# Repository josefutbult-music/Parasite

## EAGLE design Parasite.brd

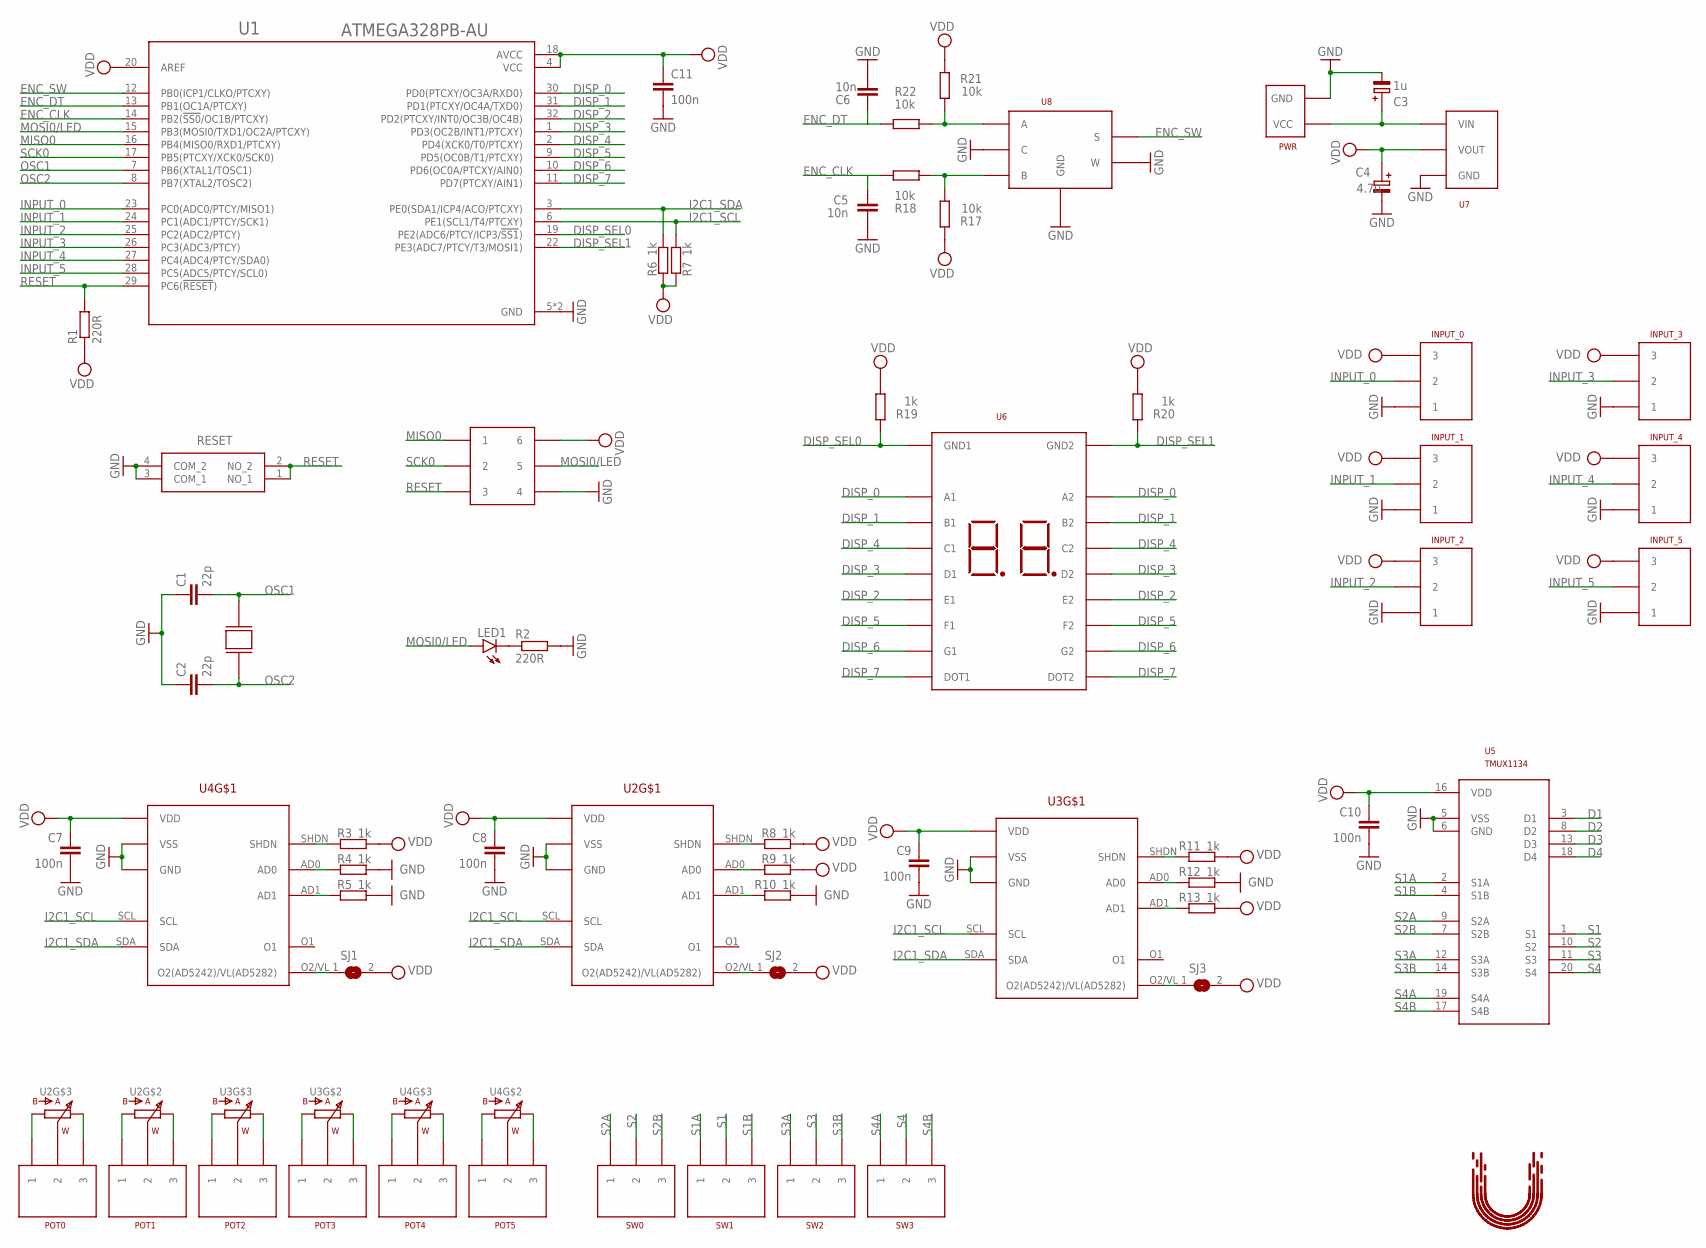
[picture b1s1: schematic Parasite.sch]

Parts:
C1, C2: 22p; C-1206
C3: 1u; UD-4X5,8_NICHICON
C4: 4.7u; UD-4X5,8_NICHICON
C5, C6: 10n; C-1206
C7, C8, C9, C10, C11: 100n; C-1206
INPUT_0, INPUT_1, INPUT_2, INPUT_3, INPUT_4, INPUT_5: 3_PIN_CONNECTOR
LED1: LEDLED_THROUGH; LED3MM
POT0, POT1, POT2, POT3, POT4, POT5: 3_PIN_CONNECTOR
PWR: PWR
R1, R2: 220R; R1206
R3, R4, R5, R6, R7, R8, R9, R10, R11, R12, R13, R19, R20: 1k; R1206
R17, R18, R21, R22: 10k; R1206
RESET: BUTTON; PTS647SK38SMTR2LFS
SJ1, SJ2, SJ3: JUMPER; SJ
SW0, SW1, SW2, SW3: 3_PIN_CONNECTOR
U1: ATMEGA328PB-AU; QFP80P900X900X120-32N
U2, U4: DIGITAL_POT_AD5242AD5242/AD5282; SOP65P640X120-16N
U3: DIGITAL_POT_AD5282AD5242/AD5282; SOP65P640X120-16N
U5: TMUX1134; SOP65P640X120-20N
U6: 7_SEGMENT_DISPLAY
U7: VOLTAGE_REGULATOR_LDL1117S50RVOLTAGE_REGULATOR_LD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; SOT230P700X180-4N
U8: ROTARY_ENCODER; ENCODER_PEC11H-4220F
U9: 3X2_PINHEADER3X2_PINHEADER; HDRV6W64P254_2X3_900X508X838B
U10: CRYSTAL_LFXTAL027946BULKCRYSTAL_LFXTAL027946BULK; XTAL1140X490X430N
U$5: UTBULT_DESIGN2; UD_2

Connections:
D1: U5.3 (D1)
D2: U5.8 (D2)
D3: U5.13 (D3)
D4: U5.18 (D4)
DISP_0: U1.30 (PD0(PTCXY/OC3A/RXD0)), U6.A1, U6.A2
DISP_1: U1.31 (PD1(PTCXY/OC4A/TXD0)), U6.B1, U6.B2
DISP_2: U1.32 (PD2(PTCXY/INT0/OC3B/OC4B)), U6.E1, U6.E2
DISP_3: U1.1 (PD3(OC2B/INT1/PTCXY)), U6.D1, U6.D2
DISP_4: U1.2 (PD4(XCK0/T0/PTCXY)), U6.C1, U6.C2
DISP_5: U1.9 (PD5(OC0B/T1/PTCXY)), U6.F1, U6.F2
DISP_6: U1.10 (PD6(OC0A/PTCXY/AIN0)), U6.G1, U6.G2
DISP_7: U1.11 (PD7(PTCXY/AIN1)), U6.DOT1, U6.DOT2
DISP_SEL0: R19.1, U1.19 (PE2(ADC6/PTCY/ICP3/!SS1!)), U6.GND1
DISP_SEL1: R20.1, U1.22 (PE3(ADC7/PTCY/T3/MOSI1)), U6.GND2
ENC_CLK: C5.P$2 (2), R18.2, U1.14 (PB2(!SS0!/OC1B/PTCXY))
ENC_DT: C6.P$2 (2), R22.2, U1.13 (PB1(OC1A/PTCXY))
ENC_SW: U1.12 (PB0(ICP1/CLKO/PTCXY)), U8.S
GND: C1.P$1 (1), C2.P$1 (1), C3.-, C4.-, C5.P$1 (1), C6.P$1 (1), C7.P$2 (2), C8.P$2 (2), C9.P$2 (2), C10.P$2 (2), C11.P$2 (2), INPUT_0.P$1 (1), INPUT_1.P$1 (1), INPUT_2.P$1 (1), INPUT_3.P$1 (1), INPUT_4.P$1 (1), INPUT_5.P$1 (1), PWR.P$2 (GND), R2.2, R4.1, R5.1, R10.1, R12.1, RESET.3 (COM_1), RESET.4 (COM_2), U1.5 (GND), U1.21 (GND), U2.GND, U2.VSS, U3.GND, U3.VSS, U4.GND, U4.VSS, U5.5 (VSS), U5.6 (GND), U7.1 (GND), U8.C, U8.GND1 (GND), U8.GND2 (GND), U8.W, U9.4
I2C1_SCL: R7.1, U1.6 (PE1(SCL1/T4/PTCXY)), U2.SCL, U3.SCL, U4.SCL
I2C1_SDA: R6.1, U1.3 (PE0(SDA1/ICP4/ACO/PTCXY)), U2.SDA, U3.SDA, U4.SDA
INPUT_0: INPUT_0.P$2 (2), U1.23 (PC0(ADC0/PTCY/MISO1))
INPUT_1: INPUT_1.P$2 (2), U1.24 (PC1(ADC1/PTCY/SCK1))
INPUT_2: INPUT_2.P$2 (2), U1.25 (PC2(ADC2/PTCY))
INPUT_3: INPUT_3.P$2 (2), U1.26 (PC3(ADC3/PTCY))
INPUT_4: INPUT_4.P$2 (2), U1.27 (PC4(ADC4/PTCY/SDA0))
INPUT_5: INPUT_5.P$2 (2), U1.28 (PC5(ADC5/PTCY/SCL0))
MISO0: U1.16 (PB4(MISO0/RXD1/PTCXY)), U9.1
MOSI0/LED: LED1.A, U1.15 (PB3(MOSI0/TXD1/OC2A/PTCXY)), U9.5
unnamed: LED1.K (C), R2.1
unnamed: R3.2, U4.SHDN
unnamed: R4.2, U4.AD0
unnamed: R5.2, U4.AD1
unnamed: SJ1.1, U4.O2/VL (O2(AD5242)/VL(AD5282))
unnamed: R11.2, U3.SHDN
unnamed: R8.2, U2.SHDN
unnamed: R9.2, U2.AD0
unnamed: R10.2, U2.AD1
unnamed: SJ2.1, U2.O2/VL (O2(AD5242)/VL(AD5282))
unnamed: R12.2, U3.AD0
unnamed: R13.2, U3.AD1
unnamed: SJ3.1, U3.O2/VL (O2(AD5242)/VL(AD5282))
unnamed: POT2.P$2 (2), U3.W2 (W)
unnamed: POT1.P$2 (2), U2.W1 (W)
unnamed: POT0.P$2 (2), U2.W2 (W)
unnamed: POT4.P$2 (2), U4.W2 (W)
unnamed: POT5.P$2 (2), U4.W1 (W)
unnamed: POT3.P$2 (2), U3.W1 (W)
unnamed: POT0.P$3 (3), U2.A2 (A)
unnamed: POT0.P$1 (1), U2.B2 (B)
unnamed: POT3.P$1 (1), U3.B1 (B)
unnamed: POT3.P$3 (3), U3.A1 (A)
unnamed: POT2.P$1 (1), U3.B2 (B)
unnamed: POT2.P$3 (3), U3.A2 (A)
unnamed: POT1.P$1 (1), U2.B1 (B)
unnamed: POT1.P$3 (3), U2.A1 (A)
unnamed: POT4.P$3 (3), U4.A2 (A)
unnamed: POT5.P$3 (3), U4.A1 (A)
unnamed: POT4.P$1 (1), U4.B2 (B)
unnamed: POT5.P$1 (1), U4.B1 (B)
unnamed: C3.+, PWR.P$1 (VCC), U7.3 (VIN)
unnamed: R17.2, R18.1, U8.B
unnamed: R21.2, R22.1, U8.A
OSC1: C1.P$2 (2), U1.7 (PB6(XTAL1/TOSC1)), U10.2
OSC2: C2.P$2 (2), U1.8 (PB7(XTAL2/TOSC2)), U10.1
RESET: R1.2, RESET.1 (NO_1), RESET.2 (NO_2), U1.29 (PC6(!RESET!)), U9.3
S1: SW1.P$2 (2), U5.1 (S1)
S1A: SW1.P$1 (1), U5.2 (S1A)
S1B: SW1.P$3 (3), U5.4 (S1B)
S2: SW0.P$2 (2), U5.10 (S2)
S2A: SW0.P$1 (1), U5.9 (S2A)
S2B: SW0.P$3 (3), U5.7 (S2B)
S3: SW2.P$2 (2), U5.11 (S3)
S3A: SW2.P$1 (1), U5.12 (S3A)
S3B: SW2.P$3 (3), U5.14 (S3B)
S4: SW3.P$2 (2), U5.20 (S4)
S4A: SW3.P$1 (1), U5.19 (S4A)
S4B: SW3.P$3 (3), U5.17 (S4B)
SCK0: U1.17 (PB5(PTCXY/XCK0/SCK0)), U9.2
VDD: C4.+, C7.P$1 (1), C8.P$1 (1), C9.P$1 (1), C10.P$1 (1), C11.P$1 (1), INPUT_0.P$3 (3), INPUT_1.P$3 (3), INPUT_2.P$3 (3), INPUT_3.P$3 (3), INPUT_4.P$3 (3), INPUT_5.P$3 (3), R1.1, R3.1, R6.2, R7.2, R8.1, R9.1, R11.1, R13.1, R17.1, R19.2, R20.2, R21.1, SJ1.2, SJ2.2, SJ3.2, U1.4 (VCC), U1.18 (AVCC), U1.20 (AREF), U2.VDD, U3.VDD, U4.VDD, U5.16 (VDD), U7.2 (VOUT), U7.4 (VOUT), U9.6

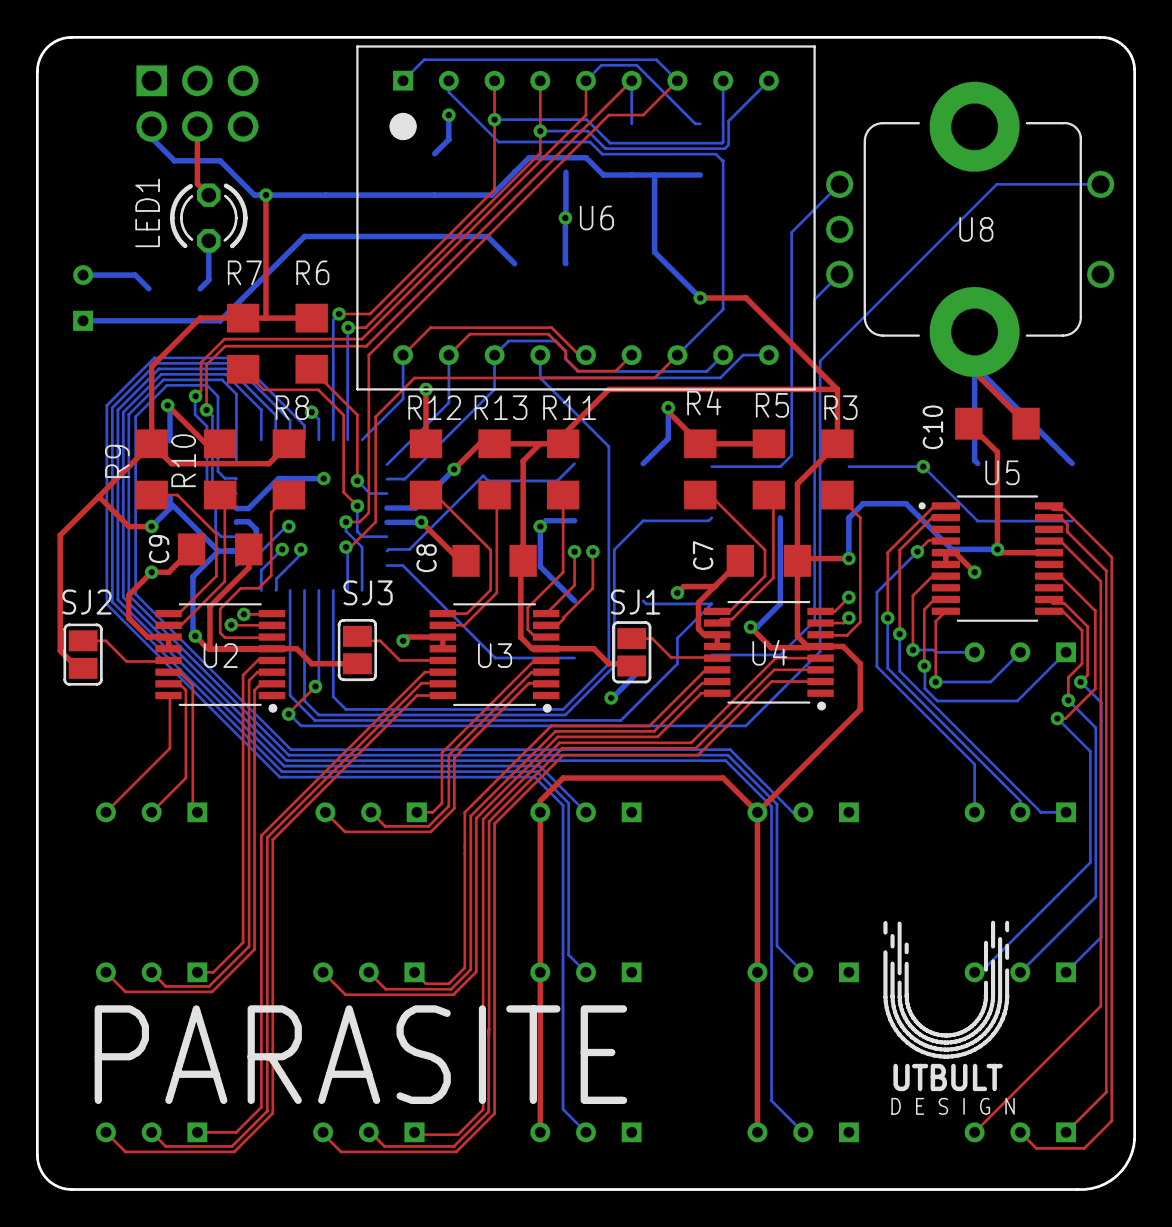
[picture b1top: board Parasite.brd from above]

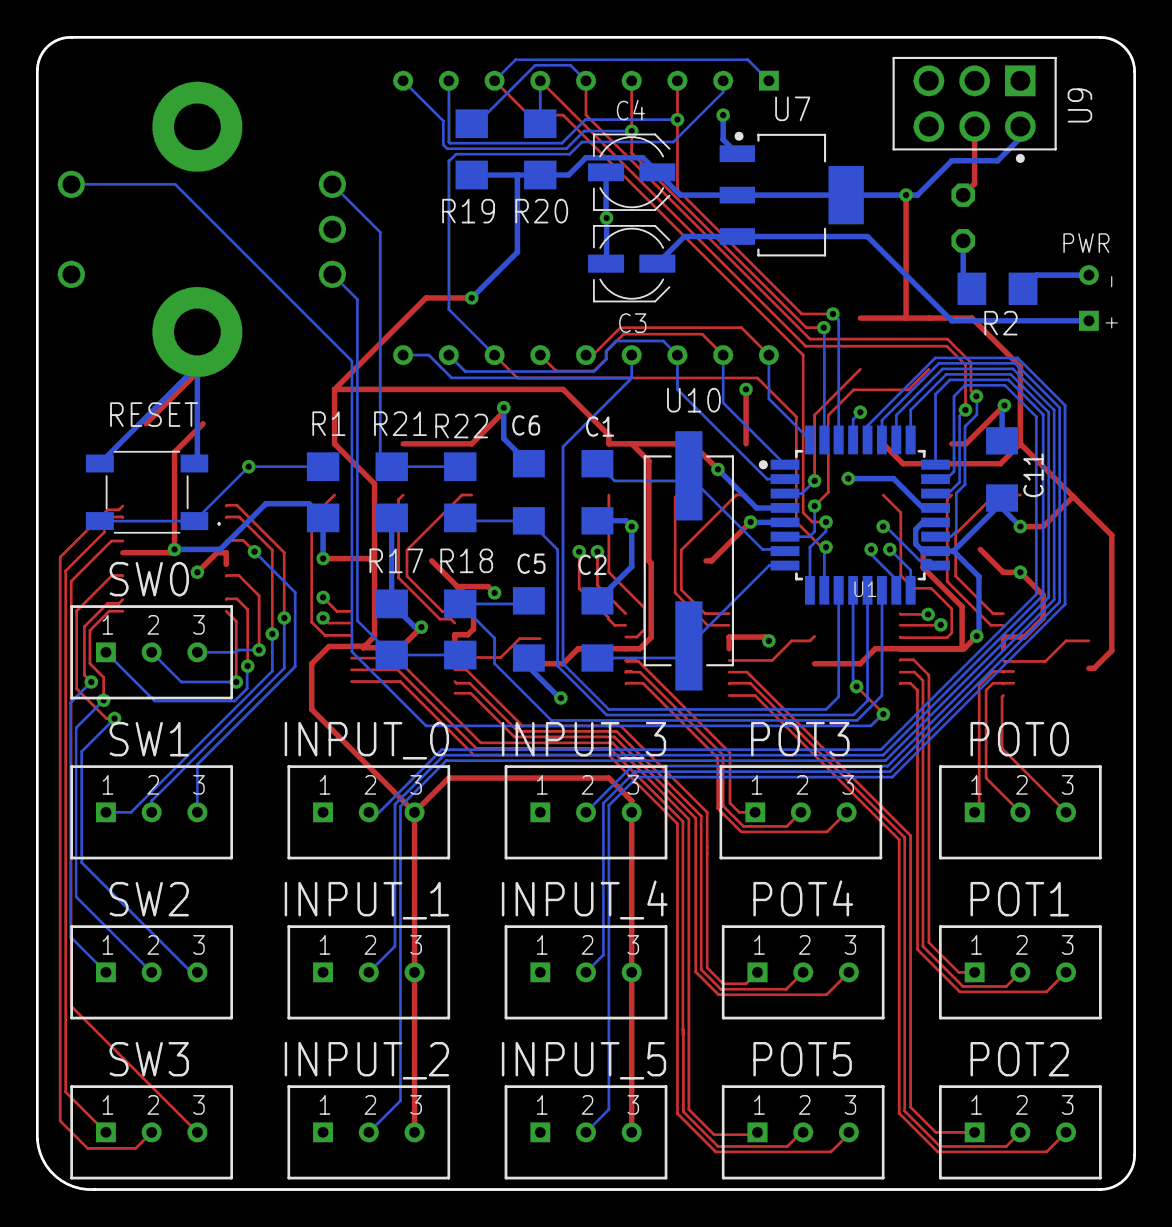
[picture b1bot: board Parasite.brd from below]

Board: 4 copper layers, 61.0 x 64.0 mm, 63 parts (37 on the bottom side), 75 nets.

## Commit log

2020-12-12 Init
2020-12-21 Added components and initialized layout
2020-12-21 Finished v1 layout
2021-02-25 Fixed interrupts for inputs
2021-02-26 Structured up map, and tried to work with I2C
2021-04-22 Fixed encoder and restructure
